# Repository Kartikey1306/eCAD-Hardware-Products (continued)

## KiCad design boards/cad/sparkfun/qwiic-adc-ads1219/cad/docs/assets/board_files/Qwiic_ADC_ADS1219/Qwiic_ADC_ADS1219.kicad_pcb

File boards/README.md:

# Boards Catalog

Development boards and kits relevant to the EmbeddedOS (EoS) ecosystem:
what the OS supports today, and where hardware/CAD work is heading.

Tracked by [#28](https://github.com/embeddedos-org/eCAD-Hardware-Products/issues/28)
("Development boards, kits, and CAD design-file reference"), which scopes the
full catalog across Arduino/AVR, Raspberry Pi, ESP32/ESP8266, STM32, Nordic,
FPGA, robotics, and AI-accelerator families.

## Boards with EoS descriptors today

These boards have first-class descriptors in
[`eos/boards/`](https://github.com/embeddedos-org/eos/tree/master/boards)
(`boards/*.yaml`: MCU, memory map, peripherals, linker script). The table
below is generated from those descriptors — the single source of truth.

| Board (descriptor) | MCU | Family | Vendor | Core |
|---|---|---|---|---|
| `am64x` | AM6442 | Sitara | Texas Instruments | cortex-a53 |
| `esp32` | ESP32-D0WDQ6 | ESP32 | Espressif | lx6 |
| `hiletgo-esp-wroom-32` | ESP32-D0WDQ6 | ESP32 | Espressif | lx6 |
| `imx8m` | MIMX8MM6 | i.MX8M | NXP | cortex-a53 |
| `nrf52840` | NRF52840 | nRF52 | Nordic Semiconductor | cortex-m4f |
| `qemu-arm64` | — | — | — | — |
| `raspberrypi4` | — | — | — | — |
| `samd51` | ATSAMD51J20A | SAMD51 | Microchip | cortex-m4f |
| `sifive_u` | FU740-C000 | HiFive | SiFive | u74 |
| `stm32f4` | STM32F407VG | STM32F4 | ST Microelectronics | cortex-m4 |
| `stm32h743` | — | — | ST Microelectronics | — |
| `stm32mp1` | — | — | ST Microelectronics | — |
| `tms570` | TMS570LC4357 | TMS570 | Texas Instruments | cortex-r5f |

("—" = not specified in the descriptor; contributions welcome.)

## Generic targets

Beyond the named boards, `eos/boards/` ships 71 `generic-*` descriptors
covering CPU families without a specific board attached (e.g.
`generic-cortex-m4`, `generic-esp32s3`, `generic-riscv*`, `generic-avr`,
`generic-8051`). These are the bring-up starting point for a new board in
the same family: copy the closest generic descriptor, fill in the concrete
MCU, memory map, and peripherals, and submit it against `eos`.

## Adding a board

1. Add `boards/<name>.yaml` in `eos` following the existing schema
   (`board.name/mcu/family/arch/core/vendor/clock_hz/memory/peripherals`).
2. If this repo should carry the CAD side (schematic, PCB, 3D model),
   open an issue here referencing the `eos` descriptor and attach the
   design files under the matching `*_CAD_Design/` domain directory.

## Incoming (no EoS descriptor yet) — October 2026

Boards on the #28 watchlist with no `eos/boards/` descriptor yet. Entries
stay here (not in the table above) until a descriptor lands; specs are
minimal until datasheet review.

| Board | Vendor | Family | Notes |
|---|---|---|---|
| FRDM-IMXRT1186 | NXP | i.MX RT1186 | FRDM dev board: M7 @ 800MHz + M33 @ 300MHz, dual GbE TSN + 2× Fast Eth (EtherCAT/TSN), motor-control headers — the eNet deterministic-comms reference target |
| ESP32-C5 Pico | Espressif | ESP32-C5 | RISC-V + 802.15.4/Wi-Fi 6; Thread/Matter candidate |
| ESP-Mosaico (S31) | — | — | Specs pending datasheet review |
| Arduino VENTUNO Q | Arduino | Dragonwing IQ-8275 + STM32H5F5 | Dual-brain: Qualcomm Dragonwing IQ-8275 + STM32H5F5, 16GB RAM, 3× MIPI-CSI, CAN FD, ROS 2 — the dual-brain pattern in hardware |
| DEBIX M8391-01 | DEBIX | MediaTek Genio 720 | Octa-core A78/A55, 9-TOPS NPU850, industrial -40..85°C, Pi-sized — mid-tier NPU vision/robotics target |
| Bluemag Pi | Upbeat | SiFive E3 + E2 | RISC-V flight controller (E3 flight-critical + E2 AI/system), onboard AI; CEATEC Oct 13–16 demo — aero dual-brain COTS reference |
| Alif StartKit SK-E1C | Alif | Ensemble E1C | Cortex-M55 + Ethos-U55, 2MB SRAM, Arducam header, dual PDM mics, onboard J-Link — tinyML reference target |
| Alif StartKit SK-B1 | Alif | Ensemble E1 | As E1C + BLE 5.3 + 802.15.4 |
| NuMaker-IoT-MA35D0-A2 "Chili Pro" | Nuvoton | MA35D0 | Dual Cortex-A35 650MHz + Cortex-M4 180MHz; 45×45mm heterogeneous Linux+MCU eval board |
| M5Stack Stamp LoRa-1262 / Module13.2 | M5Stack | ESP32-S3 | SX1262, 868–923MHz LoRa; pairs with the eNet LoRaWAN study |
| 8devices 8Sight T100 | 8devices | STM32N657 | Cortex-M55 800MHz + 600-GOPS Neural-ART NPU + HW ISP; Lynred LWIR, 320×240@60fps fully offline — NPU-vision reference design |
| AIM-M-H10 | Geniatech | Hailo-10 | M.2 2280 M-Key AI accelerator card: Hailo-10 at up to 40 TOPS, up to 16GB on-module LPDDR4/4X, PCIe host link, ~12W — the M.2-keyed accelerator pattern for M.2-bearing watchlist hosts; vendor figures per the Geniatech product page, pending datasheet review |
| AIM-M-R28 | Geniatech | Rockchip RK1828 | M.2 2280 M-Key AI accelerator card: RK1828 coprocessor at 20 TOPS INT8 with 5GB in-package DRAM, PCIe 2.1 x1, 20W TDP, -25..85°C — local LLM/VLM inference aimed at Rockchip hosts (RK3568/3576/3588); vendor figures per the Geniatech product page, pending datasheet review |
| Raspberry Pi Smart Display Module | Raspberry Pi | Compute Module 5 carrier (Intel SDM-L) | $30 CM5 carrier in the Intel SDM-L form factor, built for digital signage and kiosks: HDMI 2.0 out, GbE, M.2 M-key (NVMe or an AI accelerator), MIPI DSI/CSI-2; vendor lifecycle "available until at least January 2036". The commercial CM5-carrier counterpart to the org's original [eos-cm5-base](eos/eos-cm5-base/README.md) — not a mirror candidate (no redistributable CAD published), recorded here as the signage/kiosk reference |
| Orange Pi O1 | Orange Pi | SOPHGO BM1688 | AI-vision SBC: octa-core Cortex-A53 @ 1.65GHz + RISC-V C906 co-processor, 16 TOPS INT8 TPU, up to 16x 1080p30 decode, 8/16GB LPDDR4/X, dual GbE, Wi-Fi 6E, M.2 M-key NVMe + M.2 B-key (4G/5G) — watchlist entry, specs per CNX Software's 2026-10-15 report, pending datasheet review; the same BM1688 SoC is an eAI silicon-roster candidate |
| HPMicro HPM5151 (MCU family — no board yet) | HPMicro | HPM5100 series | Silicon-family watchlist entry, not a board record: 400 MHz RISC-V (up to 480 MHz), 416 KB SRAM, 1 MB flash, 4× 16-bit ADCs, 4× op-amps, 4× comparators, USB 2.0 OTG + PHY, CAN FD, 32 PWM channels, HW FPU/SIMD/DSP, 3.57 CoreMark/MHz — motor-control / mixed-signal analog niche; specs per CNX Software's report, pending datasheet review |

## Design files

[`cad/`](cad/) holds the published CAD design of every catalogued board whose licence
allows redistribution: every CAD file in the manufacturer's repository at the commit its
record pins, in the manufacturer's folder layout. That means Eagle, KiCad, Altium, OrCAD
and Allegro sources, projects and libraries, Gerber and drill files, and STEP, IGES, STL,
VRML and DXF models; archives are unpacked to their CAD members. Each file is
byte-identical to its recorded digest or to its git blob at that commit, and each board's
`ATTRIBUTION.md` credits the manufacturer, names the licence and lists what was left out.
Documents (PDFs, BOMs, readmes) are never copied. How it is built and checked:
[docs/devboard-cad-database.md](../docs/devboard-cad-database.md#mirror).

## Roadmap (from #28)

- Per-family pages (Arduino, Pi, ESP32, STM32, nRF, FPGA, robotics kits)
  with CAD design-file references.
- Mapping each catalog entry to its EoS support tier (descriptor,
  BSP, EoSim model).
- Kit/cookbook entries: "what to buy to run EoS on <board>".

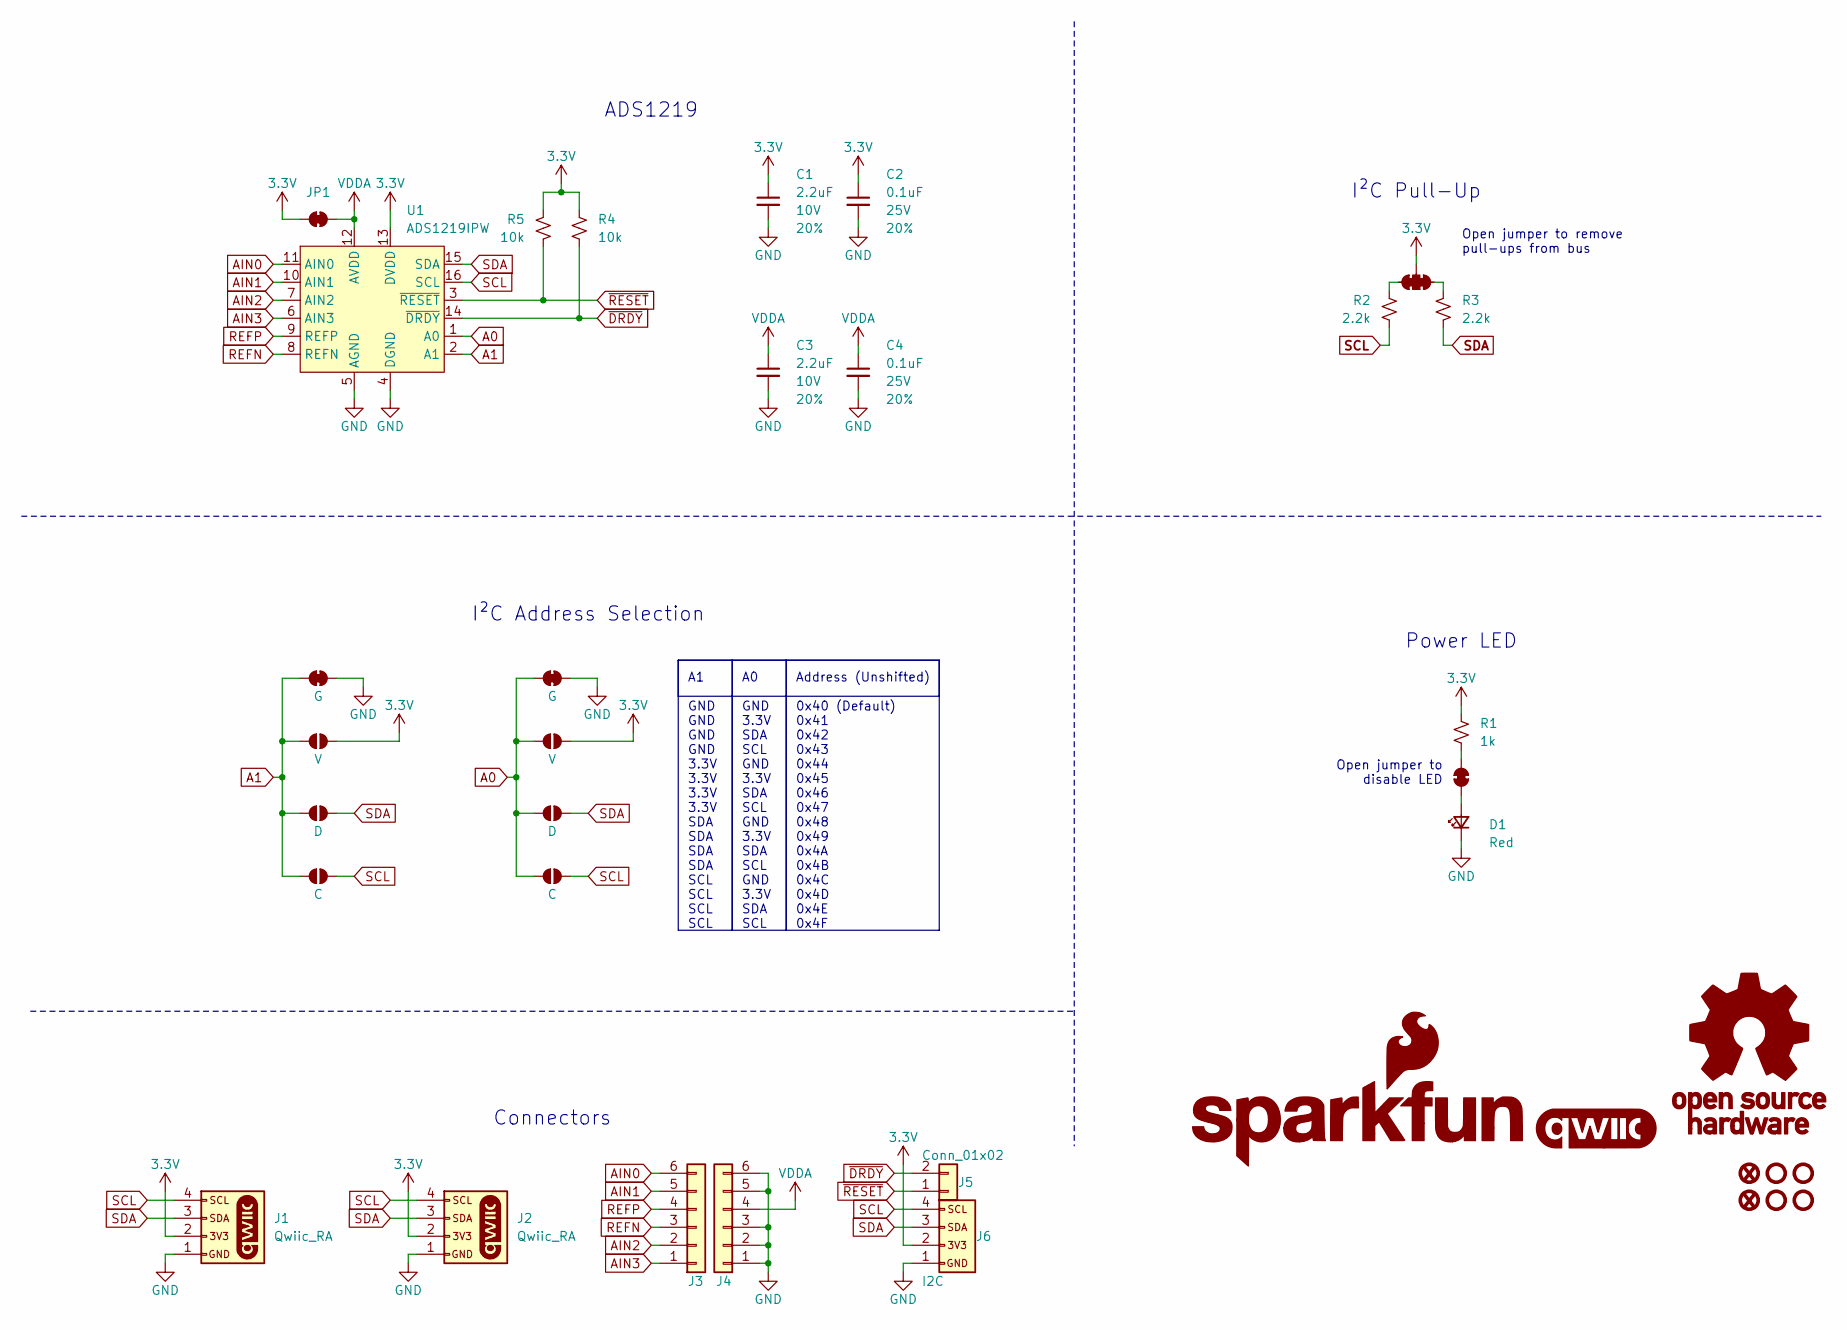
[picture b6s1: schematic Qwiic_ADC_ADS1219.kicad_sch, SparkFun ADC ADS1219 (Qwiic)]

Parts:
C1, C3: 2.2uF; C_0603_1608Metric; Voltage 10V; Tolerance 20%
C2, C4: 0.1uF; C_0603_1608Metric; Voltage 25V; Tolerance 20%
D1: Red; LED_0603_1608Metric_Red
FID1, FID3: Fiducial_0.5mm; Fiducial_0.5mm_Mask1mm
G1: SparkFun_Logo
J1, J2: Qwiic_RA; JST_SMD_1.0mm-4_Black
J3, J4: Conn_01x06; 1x06
J5: Conn_01x02; 1x02
J6: I2C; 1x04
JP1, JP2: Jumper_2_NC_Trace
JP3: Jumper_3_NC-2_Trace
JP4, JP8: G; Jumper_2_NC_Trace
JP5, JP9: V; Jumper_2_NO
JP6, JP10: D; Jumper_2_NO
JP7, JP11: C; Jumper_2_NO
R1: 1k; R_0603_1608Metric
R2, R3: 2.2k; R_0603_1608Metric
R4, R5: 10k; R_0603_1608Metric
ST1, ST2, ST3, ST4: Standoff
U1: ADS1219IPW; TSSOP-16

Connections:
3.3V: C1.1, C2.1, J1.2, J2.2, J6.2, JP1.1 (A), JP3.2 (B), JP5.2 (B), JP9.2 (B), R1.2, R4.2, R5.1, U1.13 (DVDD)
A0: JP4.1 (A), JP5.1 (A), JP6.1 (A), JP7.1 (A), U1.1 (A0)
A1: JP8.1 (A), JP9.1 (A), JP10.1 (A), JP11.1 (A), U1.2 (A1)
AIN0: J3.6, U1.11 (AIN0)
AIN1: J3.5, U1.10 (AIN1)
AIN2: J3.2, U1.7 (AIN2)
AIN3: J3.1, U1.6 (AIN3)
GND: C1.2, C2.2, C3.2, C4.2, D1.1 (K), J1.1, J2.1, J4.1, J4.2, J4.3, J4.5, J4.6, J6.1, JP4.2 (B), JP8.2 (B), U1.4 (DGND), U1.5 (AGND)
unnamed: D1.2 (A), JP2.1 (A)
unnamed: JP2.2 (B), R1.1
unnamed: JP3.1 (A), R3.1
unnamed: JP3.3 (C), R2.2
REFN: J3.3, U1.8 (REFN)
REFP: J3.4, U1.9 (REFP)
SCL: J1.4, J2.4, J6.4, JP7.2 (B), JP11.2 (B), R2.1, U1.16 (SCL)
SDA: J1.3, J2.3, J6.3, JP6.2 (B), JP10.2 (B), R3.2, U1.15 (SDA)
VDDA: C3.1, C4.1, J4.4, JP1.2 (B), U1.12 (AVDD)
~DRDY: J5.2, R4.1, U1.14 (~DRDY)
~RESET: J5.1, R5.2, U1.3 (~RESET)

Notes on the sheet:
Open jumper to remove pull-ups from bus
Connectors
Power LED
I²C Address Selection
Open jumper to disable LED
A1 GND GND GND GND 3.3V 3.3V 3.3V 3.3V SDA SDA SDA SDA SCL SCL SCL SCL
Address (Unshifted) 0x40 (Default) 0x41 0x42 0x43 0x44 0x45 0x46 0x47 0x48 0x49 0x4A 0x4B 0x4C 0x4D 0x4E 0x4F
ADS1219
I²C Pull-Up
A0 GND 3.3V SDA SCL GND 3.3V SDA SCL GND 3.3V SDA SCL GND 3.3V SDA SCL

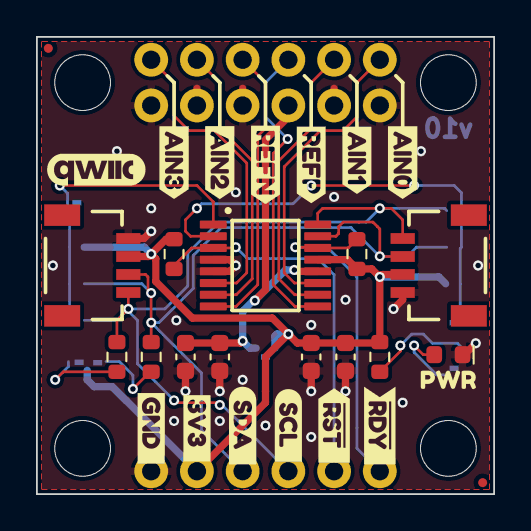
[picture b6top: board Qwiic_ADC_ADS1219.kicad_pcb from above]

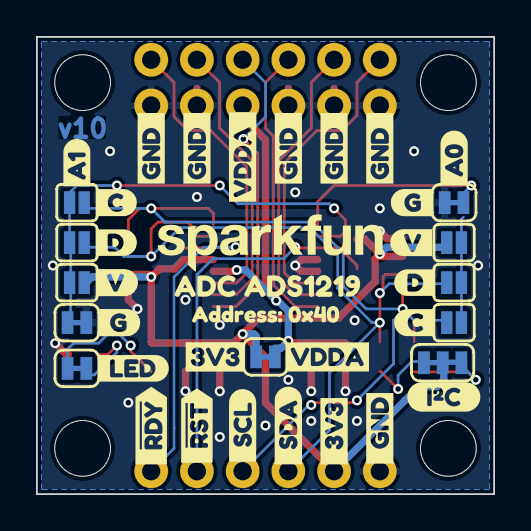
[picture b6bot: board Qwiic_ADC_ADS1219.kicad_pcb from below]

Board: 2 copper layers, 25.4 x 25.4 mm, 75 parts (39 on the bottom side), 19 nets.

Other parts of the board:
kibuzzard-64C3B30F: G***; kibuzzard-64C3B30F
kibuzzard-64C3BD7A: G***; kibuzzard-64C3BD7A
kibuzzard-64C36D1A: G***; kibuzzard-64C36D1A
kibuzzard-64C36D2D: G***; kibuzzard-64C36D2D
kibuzzard-64C36D5B: G***; kibuzzard-64C36D5B
kibuzzard-64C36D6C: G***; kibuzzard-64C36D6C
kibuzzard-64C36D47: G***; kibuzzard-64C36D47
kibuzzard-64C36D91: G***; kibuzzard-64C36D91
kibuzzard-64C37A88: G***; kibuzzard-64C37A88
kibuzzard-64C37CC9: G***; kibuzzard-64C37CC9
kibuzzard-64C38090: G***; kibuzzard-64C38090
kibuzzard-67BCC03F: G***; kibuzzard-67BCC03F
kibuzzard-67BCE7E0: G***; kibuzzard-67BCE7E0
kibuzzard-67BCE9A5: G***; kibuzzard-67BCE9A5
kibuzzard-67BCE9C9: G***; kibuzzard-67BCE9C9
kibuzzard-67BCE9CD: G***; kibuzzard-67BCE9CD
kibuzzard-67BCE9E1: G***; kibuzzard-67BCE9E1
kibuzzard-67BCE80E: G***; kibuzzard-67BCE80E
kibuzzard-67BCE89D: G***; kibuzzard-67BCE89D
kibuzzard-67BCE805: G***; kibuzzard-67BCE805
kibuzzard-67BCE809: G***; kibuzzard-67BCE809
kibuzzard-67BCE889: G***; kibuzzard-67BCE889
kibuzzard-67BCE896: G***; kibuzzard-67BCE896
kibuzzard-67BCE899: G***; kibuzzard-67BCE899
kibuzzard-67BCEA1E: G***; kibuzzard-67BCEA1E
kibuzzard-67BCEA3A: G***; kibuzzard-67BCEA3A
kibuzzard-67BCEA31: G***; kibuzzard-67BCEA31
kibuzzard-67BCEA48: G***; kibuzzard-67BCEA48
kibuzzard-67BCEA55: G***; kibuzzard-67BCEA55
kibuzzard-67BCEA65: G***; kibuzzard-67BCEA65
kibuzzard-67BCEA70: G***; kibuzzard-67BCEA70
kibuzzard-67BCEAAB: G***; kibuzzard-67BCEAAB
kibuzzard-67BCEAC6, kibuzzard-67BCEAC6#2, kibuzzard-67BCEAC6#3, kibuzzard-67BCEAC6#4, kibuzzard-67BCEAC6#5: G***; kibuzzard-67BCEAC6
kibuzzard-67BCEAE1: G***; kibuzzard-67BCEAE1
kibuzzard-67BCEB1D: G***; kibuzzard-67BCEB1D
kibuzzard-67BCEB15: G***; kibuzzard-67BCEB15
kibuzzard-67BCEB32: G***; kibuzzard-67BCEB32

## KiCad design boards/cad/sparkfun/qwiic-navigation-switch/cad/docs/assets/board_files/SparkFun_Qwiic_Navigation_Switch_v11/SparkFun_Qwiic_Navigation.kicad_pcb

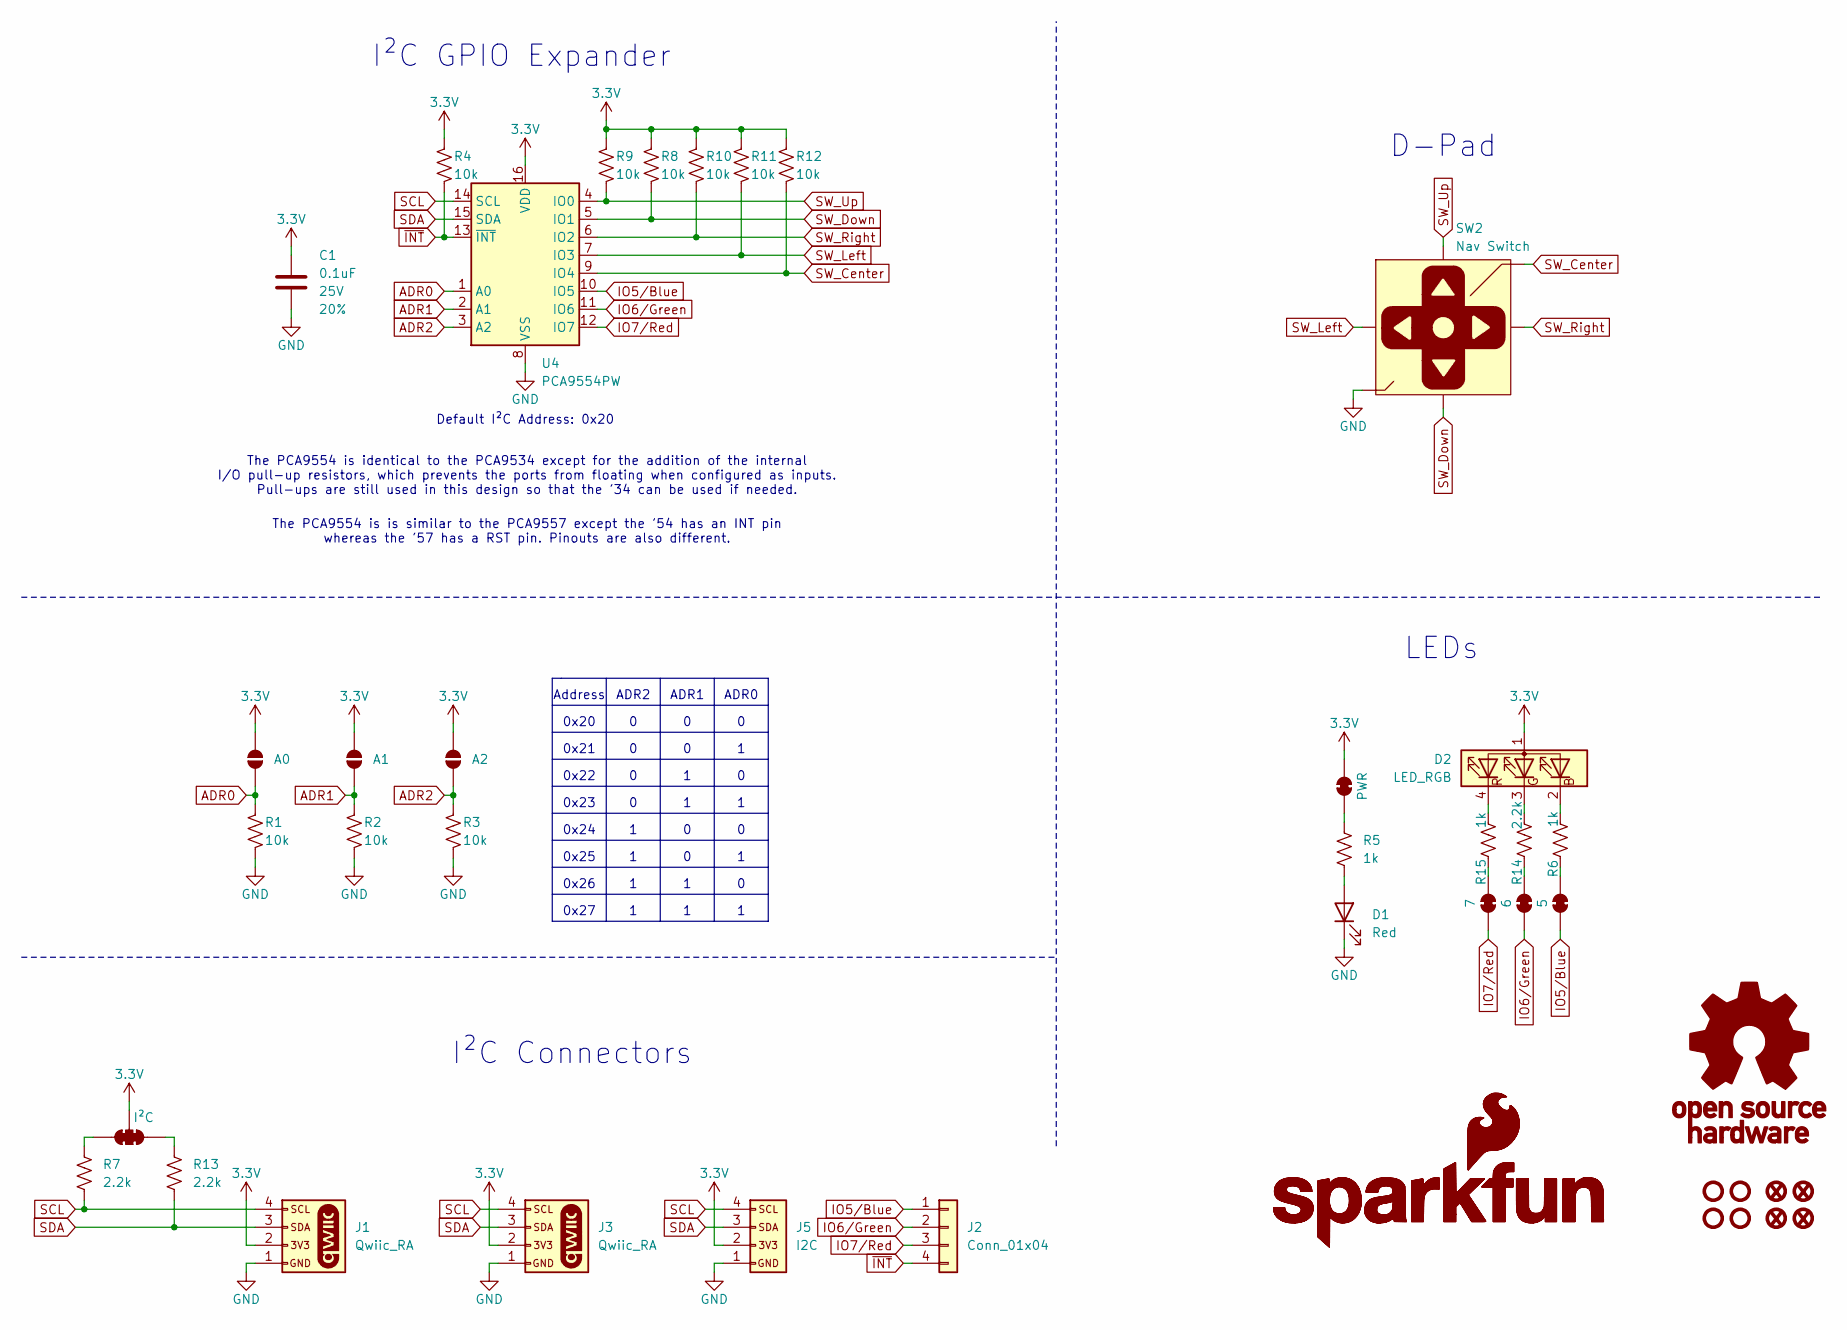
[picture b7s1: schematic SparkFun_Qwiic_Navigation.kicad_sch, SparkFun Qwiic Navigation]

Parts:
C1: 0.1uF; C_0603_1608Metric; Voltage 25V; Tolerance 20%
D1: Red; LED_0603_1608Metric_Red
D2: LED_RGB; LED_1205_RGB_Bottom
FID1, FID2, FID3, FID4: Fiducial_0.5mm; Fiducial_0.5mm_Mask1mm
G1: OSHW_Logo; Creative_Commons_License
G3: SparkFun_Logo
G5: SparkFun_Logo; SparkFun_Logo_8mm
J1, J3: Qwiic_RA; JST_SMD_1.0mm-4_RA
J2: Conn_01x04; 1x04
J5: I2C; 1x04
JP1: A0; Jumper_2_NO
JP2: A1; Jumper_2_NO
JP3: A2; Jumper_2_NO
JP4: PWR; Jumper_2_NC_Trace
JP5: 5; Jumper_2_NC_Trace
JP6: I²C; Jumper_3_NC-2_Trace
JP7: 6; Jumper_2_NC_Trace
JP8: 7; Jumper_2_NC_Trace
R1, R2, R3, R4, R8, R9, R10, R11, R12: 10k; R_0603_1608Metric
R5, R6, R15: 1k; R_0603_1608Metric
R7, R13, R14: 2.2k; R_0603_1608Metric
ST1, ST2, ST3, ST4: Standoff
SW2: Nav Switch; Navigation_SMD_7.5x7.5mm
U4: PCA9554PW; TSSOP-16_4.4x5mm_P0.65mm

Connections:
3.3V: C1.1, D2.1 (A), J1.2, J3.2, J5.2, JP1.2 (B), JP2.2 (B), JP3.2 (B), JP4.2 (B), JP6.2 (C), R4.2, R8.2, R9.2, R10.2, R11.2, R12.2, U4.16 (VDD)
ADR0: JP1.1 (A), R1.2, U4.1 (A0)
ADR1: JP2.1 (A), R2.2, U4.2 (A1)
ADR2: JP3.1 (A), R3.2, U4.3 (A2)
GND: C1.2, D1.1 (K), J1.1, J3.1, J5.1, R1.1, R2.1, R3.1, SW2.2 (GND), U4.8 (VSS)
IO5/Blue: J2.1, JP5.2 (B), U4.10 (IO5)
IO6/Green: J2.2, JP7.2 (B), U4.11 (IO6)
IO7/Red: J2.3, JP8.2 (B), U4.12 (IO7)
unnamed: D1.2 (A), R5.2
unnamed: D2.2 (BK), R6.2
unnamed: D2.3 (GK), R14.2
unnamed: D2.4 (RK), R15.2
unnamed: JP4.1 (A), R5.1
unnamed: JP5.1 (A), R6.1
unnamed: JP6.1 (A), R13.1
unnamed: JP6.3 (B), R7.1
unnamed: JP7.1 (A), R14.1
unnamed: JP8.1 (A), R15.1
SCL: J1.4, J3.4, J5.4, R7.2, U4.14 (SCL)
SDA: J1.3, J3.3, J5.3, R13.2, U4.15 (SDA)
SW_Center: R12.1, SW2.5 (Center), U4.9 (IO4)
SW_Down: R8.1, SW2.3 (Down), U4.5 (IO1)
SW_Left: R11.1, SW2.1 (Left), U4.7 (IO3)
SW_Right: R10.1, SW2.4 (Right), U4.6 (IO2)
SW_Up: R9.1, SW2.6 (Up), U4.4 (IO0)
~INT: J2.4, R4.1, U4.13 (~INT)

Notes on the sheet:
The PCA9554 is is similar to the PCA9557 except the '54 has an INT pin whereas the '57 has a RST pin. Pinouts are also different.
Default I²C Address: 0x20
I²C GPIO Expander
0x20
I²C Connectors
ADR2
ADR0
0x23
The PCA9554 is identical to the PCA9534 except for the addition of the internal I/O pull-up resistors, which prevents the ports from floating when configured as inputs. Pull-ups are still used in this design so that the '34 can be used if needed.
0x22
LEDs
0x25
0x26
0x24
D-Pad
0x27
ADR1
0x21
Address

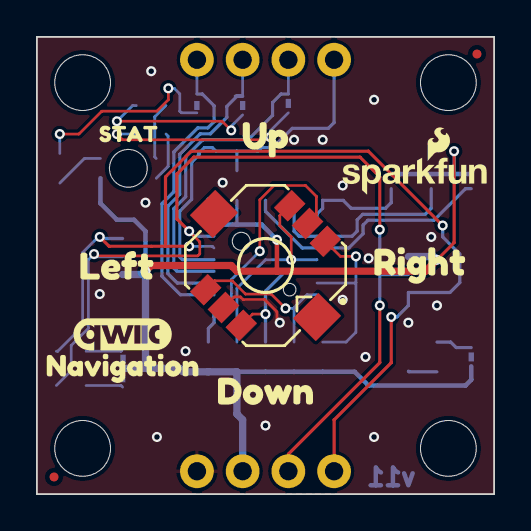
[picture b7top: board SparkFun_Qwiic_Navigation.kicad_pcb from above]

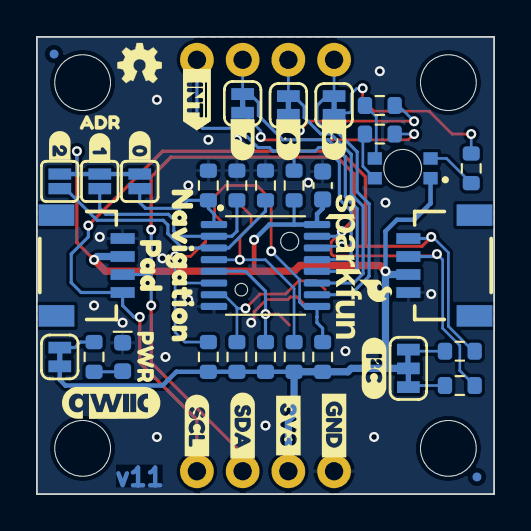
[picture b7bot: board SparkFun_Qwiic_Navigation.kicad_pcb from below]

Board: 2 copper layers, 25.4 x 25.4 mm, 64 parts (48 on the bottom side), 26 nets.

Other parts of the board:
Ref**: Val**; OSHW_Logo_2.5mm
kibuzzard-64C2E6A3: G***; kibuzzard-64C2E6A3
kibuzzard-66EED5D2: G***; kibuzzard-66EED5D2
kibuzzard-66EF6B89: G***; kibuzzard-66EF6B89
kibuzzard-66EF7A0B: G***; kibuzzard-66EF7A0B
kibuzzard-66EF7A03: G***; kibuzzard-66EF7A03
kibuzzard-66EF7A24: G***; kibuzzard-66EF7A24
kibuzzard-66EF7AE6: G***; kibuzzard-66EF7AE6
kibuzzard-66EF7AEF: G***; kibuzzard-66EF7AEF
kibuzzard-66EF7B1E: G***; kibuzzard-66EF7B1E
kibuzzard-66EF7B7C: G***; kibuzzard-66EF7B7C
kibuzzard-66EF7B15: G***; kibuzzard-66EF7B15
kibuzzard-66EF55AC: G***; kibuzzard-66EF55AC
kibuzzard-66EF79E9: G***; kibuzzard-66EF79E9
kibuzzard-66EF559E: G***; kibuzzard-66EF559E
kibuzzard-66EF5597: G***; kibuzzard-66EF5597
kibuzzard-66F18F5E: G***; kibuzzard-66F18F5E
kibuzzard-66F18F8F: G***; kibuzzard-66F18F8F
kibuzzard-66F18F9B: G***; kibuzzard-66F18F9B
kibuzzard-66F182A6: G***; kibuzzard-66F182A6
kibuzzard-675B45F7: G***; kibuzzard-675B45F7
kibuzzard-67117BDD: G***; kibuzzard-67117BDD
kibuzzard-6730262A: G***; kibuzzard-6730262A

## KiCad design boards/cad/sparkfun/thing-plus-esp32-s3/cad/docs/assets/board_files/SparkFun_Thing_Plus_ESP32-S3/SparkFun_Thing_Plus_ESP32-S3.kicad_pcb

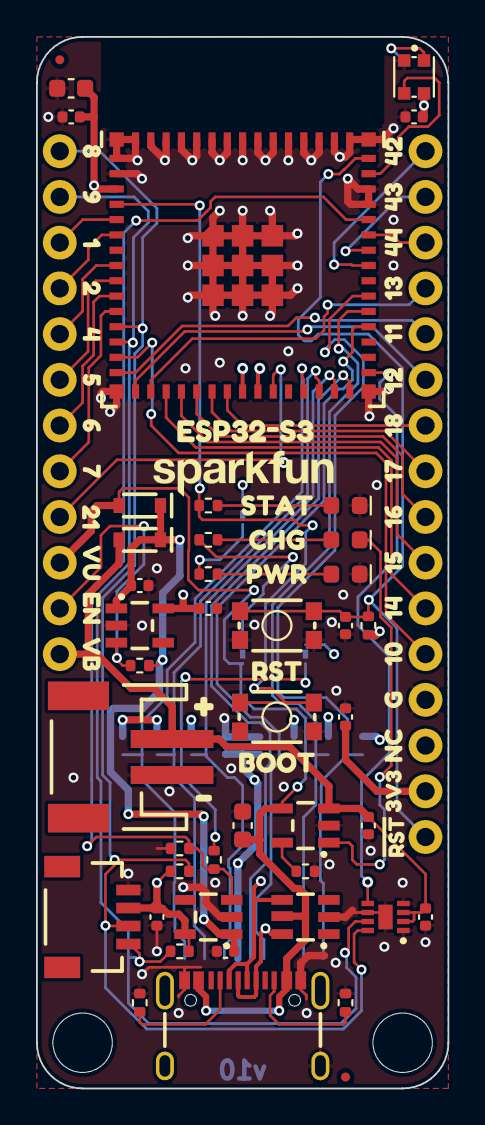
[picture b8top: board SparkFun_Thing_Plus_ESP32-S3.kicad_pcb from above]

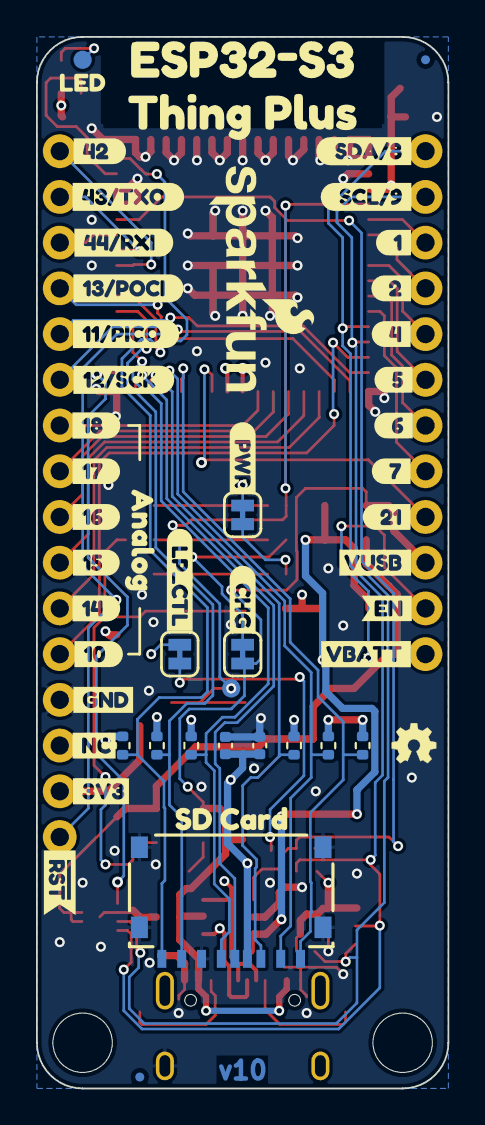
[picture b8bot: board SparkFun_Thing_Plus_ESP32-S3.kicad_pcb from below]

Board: 4 copper layers, 22.9 x 58.4 mm, 137 parts (53 on the bottom side), 53 nets.

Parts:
C1: 22uF; C_0603_1608Metric
C2, C5, C8, C11: 0.1uF; C_0402_1005Metric
C3, C4: 10uF; C_0402_1005Metric
C6, C13: 1.0uF; C_0402_1005Metric
C7, C12: 4.7uF; C_0402_1005Metric
C9: 4.7uF; C_0603_1608Metric
C10, C14: 2.2uF; C_0402_1005Metric
D1: Green; LED_0603_1608Metric
D2, D3: BAT60A; SOD-323
D4: Yellow; LED_0603_1608Metric
D5: Red; LED_0603_1608Metric
D6: WS2812B; WS2812-2020
FID1, FID2, FID3, FID4: Fiducial_0.5mm; Fiducial_0.5mm_Mask1mm
G3: OSHW_Logo; Creative_Commons_License
J1: USB_C_Receptacle; USB-C_16
J2: microSD_Friction; microSD_Friction_Fit_Atom
J3: JST_2mm_LiPo; JST_SMD_2.0mm-2
J4: Qwiic_RA; JST_SMD_1.0mm-4_RA
JP1, JP2, JP3: Jumper_2_NC_Trace
R1, R2, R3, R4, R5, R6, R8, R17: 10k; R_0402_1005Metric
R7: 330; R_0402_1005Metric
R9: 4.7k; R_0402_1005Metric
R10, R11: 5.1k; R_0402_1005Metric
R12, R15: 2.2k; R_0402_1005Metric
R13, R19: 100k; R_0402_1005Metric
R14: 1k; R_0402_1005Metric
R16: 2.0k; R_0402_1005Metric
Ref**: Val**; OSHW_Logo_2.5mm
ST1, ST3: Standoff
SW1, SW2: SMD_4.6x2.8mm_h2.5mm; Momentary_SMD_4.6x2.8mm_h2.5mm
TP1, TP2: 1.0mm; TestPoint-1.0mm
U1, U6: RT9080-3.3; SOT23-5
U2: DT1042-04SO; SOT23-6
U3: ESP32-S3-MINI; ESP32-MINI
U4: MAX17048; DFN-8
U5: MCP73831; SOT23-5
U9: Ordering_Instructions
U10: ThingPlus
kibuzzard-65A99A9C: G***; kibuzzard-65A99A9C
kibuzzard-65A99AA3: G***; kibuzzard-65A99AA3
kibuzzard-65A99E72: G***; kibuzzard-65A99E72
kibuzzard-65A403E0: G***; kibuzzard-65A403E0
kibuzzard-65A992E3: G***; kibuzzard-65A992E3
kibuzzard-65A9923A: G***; kibuzzard-65A9923A
kibuzzard-65A9926C: G***; kibuzzard-65A9926C
kibuzzard-65A9926F: G***; kibuzzard-65A9926F
kibuzzard-65A9927C: G***; kibuzzard-65A9927C
kibuzzard-65A9927F: G***; kibuzzard-65A9927F
kibuzzard-65A9928A: G***; kibuzzard-65A9928A
kibuzzard-65A9928E: G***; kibuzzard-65A9928E
kibuzzard-65A9933C: G***; kibuzzard-65A9933C
kibuzzard-65A9934B: G***; kibuzzard-65A9934B
kibuzzard-65A9935C: G***; kibuzzard-65A9935C
kibuzzard-65A9936B: G***; kibuzzard-65A9936B
kibuzzard-65A9990D: G***; kibuzzard-65A9990D
kibuzzard-65A99252: G***; kibuzzard-65A99252
kibuzzard-65A99268: G***; kibuzzard-65A99268
kibuzzard-65A99274: G***; kibuzzard-65A99274
kibuzzard-65A99278: G***; kibuzzard-65A99278
kibuzzard-65A99283: G***; kibuzzard-65A99283
kibuzzard-65A99287: G***; kibuzzard-65A99287
kibuzzard-65A99292: G***; kibuzzard-65A99292
kibuzzard-65A99297: G***; kibuzzard-65A99297
kibuzzard-65A99335: G***; kibuzzard-65A99335
kibuzzard-65A99346: G***; kibuzzard-65A99346
kibuzzard-65A99350: G***; kibuzzard-65A99350
kibuzzard-65A99354: G***; kibuzzard-65A99354
kibuzzard-65A99359: G***; kibuzzard-65A99359
kibuzzard-65A99360: G***; kibuzzard-65A99360
kibuzzard-65A99364: G***; kibuzzard-65A99364
kibuzzard-65A99367: G***; kibuzzard-65A99367
kibuzzard-65A99912: G***; kibuzzard-65A99912
kibuzzard-65A99933: G***; kibuzzard-65A99933
kibuzzard-65AA9C9F: G***; kibuzzard-65AA9C9F
kibuzzard-656A3D93: G***; kibuzzard-656A3D93
kibuzzard-656A31AF: G***; kibuzzard-656A31AF
kibuzzard-656A32A0: G***; kibuzzard-656A32A0
kibuzzard-656A32FE: G***; kibuzzard-656A32FE
kibuzzard-656A35A5: G***; kibuzzard-656A35A5
kibuzzard-656A35AD: G***; kibuzzard-656A35AD
kibuzzard-656A35B5: G***; kibuzzard-656A35B5
kibuzzard-656A35BC: G***; kibuzzard-656A35BC
kibuzzard-656A35C4: G***; kibuzzard-656A35C4
kibuzzard-656A36A2: G***; kibuzzard-656A36A2
kibuzzard-656A36A7: G***; kibuzzard-656A36A7
kibuzzard-656A36C2: G***; kibuzzard-656A36C2
kibuzzard-656A47C5: G***; kibuzzard-656A47C5
kibuzzard-656A359E: G***; kibuzzard-656A359E
kibuzzard-656A361F: G***; kibuzzard-656A361F
kibuzzard-656A367B: G***; kibuzzard-656A367B
kibuzzard-656A368C: G***; kibuzzard-656A368C
kibuzzard-656A482A: G***; kibuzzard-656A482A
kibuzzard-656A3526: G***; kibuzzard-656A3526
kibuzzard-656A3552: G***; kibuzzard-656A3552
kibuzzard-656A3559: G***; kibuzzard-656A3559
kibuzzard-656A3560: G***; kibuzzard-656A3560
kibuzzard-656A3567: G***; kibuzzard-656A3567
kibuzzard-656A3591: G***; kibuzzard-656A3591
kibuzzard-656A3598: G***; kibuzzard-656A3598
kibuzzard-656A3668: G***; kibuzzard-656A3668
kibuzzard-656A3687: G***; kibuzzard-656A3687
kibuzzard-656A3691: G***; kibuzzard-656A3691
kibuzzard-656A3878: G***; kibuzzard-656A3878
kibuzzard-656A4896: G***; kibuzzard-656A4896
kibuzzard-6569BE4A: G***; kibuzzard-6569BE4A
kibuzzard-6569BE28: G***; kibuzzard-6569BE28
kibuzzard-6569BE57: G***; kibuzzard-6569BE57
kibuzzard-6569BF02: G***; kibuzzard-6569BF02
kibuzzard-6569F7FC: G***; kibuzzard-6569F7FC
kibuzzard-6569F8A4: G***; kibuzzard-6569F8A4

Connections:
3.3V: C1.2, C7.1, C11.1, C13.1, JP1.2 (B), JP2.2 (B), R8.1, U3.3 (3V3), U6.5 (VOUT), U10.27 (3.3V)
3.3V_P: C3.1, C4.1, C5.1, C8.1, D6.4 (VDD), J2.4 (VDD), J4.2, R1.1, R2.1, R3.1, R4.1, R5.1, R6.1, R12.1, R15.1, U1.5 (VOUT)
EN: R13.2, U6.3 (EN), U10.11 (EN)
ESP0/STAT: R7.1, SW1.1 (A), TP2.1, U3.4 (IO0)
ESP1: U3.5 (IOA1), U10.3 (GPIO6)
ESP2: U3.6 (IOA2), U10.4 (GPIO5)
ESP4: U3.8 (IOA4), U10.5 (GPIO4)
ESP5: U3.9 (IOA5), U10.6 (GPIO3)
ESP6: U3.10 (IOA6), U10.7 (GPIO2)
ESP7: U3.11 (IOA7), U10.8 (GPIO1)
ESP8/SDA: J4.3, R15.2, U3.12 (IOA8), U4.8 (SDA), U10.1 (SDA)
ESP9/SCL: J4.4, R12.2, U3.13 (IOA9), U4.7 (SCL), U10.2 (SCL)
ESP10/A0: U3.14 (IOA10), U10.24 (A0)
ESP11/PICO: U3.15 (IOA11), U10.17 (PICO)
ESP12/SCK: U3.16 (IOA12), U10.18 (SCK)
ESP13/POCI: U3.17 (IOA13), U10.16 (POCI)
ESP14/A1: U3.18 (IOA14), U10.23 (A1)
ESP15/A2: U3.19 (IOA15), U10.22 (A2)
ESP16/A3: U3.20 (IOA16), U10.21 (A3)
ESP17/A4: U3.21 (IOA17), U10.20 (A4)
ESP18/A5: U3.22 (IOA18), U10.19 (A5)
ESP19/D-: J1.A7 (D-), J1.B7 (D-), U2.4 (I/O3), U3.23 (IOA19)
ESP20/D+: J1.A6 (D+), J1.B6 (D+), U2.6 (I/O4), U3.24 (IOA20)
ESP21: U3.25 (IO21), U10.9 (GPIO0)
ESP33/SDIO3: J2.2 (DAT3/~CS), R6.2, U3.28 (IO33)
ESP34/SDIO_CMD: J2.3 (CMD/SDI), R1.2, U3.29 (IO34)
ESP35/~ALRT: U3.31 (IO35), U4.5 (~ALRT)
ESP38/SDIO_CLK: J2.5 (CLK/SCK), R2.2, U3.34 (IO38)
ESP39/SDIO0: J2.7 (DAT0/SDO), R3.2, U3.35 (IO39)
ESP40/SDIO1: J2.8 (DAT1), R4.2, U3.36 (IO40)
ESP42/FREE: U3.38 (IO42), U10.13 (FREEBIE)
ESP43/TXO: U3.39 (TXD0/IO43), U10.14 (TX)
ESP44/RXI: U3.40 (RXD0/IO44), U10.15 (RX)
ESP45/Q_EN: R17.2, R19.1, U1.3 (EN), U3.41 (IO45)
ESP46/LED: D6.3 (DIN), U3.44 (IO46)
ESP47/SDIO2: J2.1 (DAT2), R5.2, U3.27 (IO47)
ESP48/SDIO_~DET: J2.9 (DET), U3.30 (IO48)
ESP~RST: C6.1, R8.2, SW2.1 (A), U3.45 (EN), U10.28 (~RESET)
GND: C1.1, C2.2, C3.2, C4.2, C5.2, C6.2, C7.2, C8.2, C9.2, C10.2, C11.2, C12.2, C13.2, C14.2, D1.1 (K), D5.1 (K), D6.2 (VSS), J1.GND, J1.S (SHIELD), J2.6 (VSS), J2.10 (SHIELD), J3.1 (-), J4.1, R10.1, R11.2, R16.2, R19.2, SW1.2 (B), SW2.2 (B), U1.2 (GND), U2.2 (GND), U3.1 (GND), U3.2 (GND), U3.42 (GND), U3.43 (GND), U3.46 (GND), U3.47 (GND), U3.48 (GND), U3.49 (GND), U3.50 (GND), U3.51 (GND), U3.52 (GND), U3.53 (GND), U3.54 (GND), U3.55 (GND), U3.56 (GND), U3.57 (GND), U3.58 (GND), U3.59 (GND), U3.60 (GND), U3.61 (GND), U3.62 (GND), U3.63 (GND), U3.64 (GND), U3.65 (GND), U4.1 (CTG), U4.4 (GND), U4.6 (QSTRT), U4.9 (GND), U5.2 (GND), U6.2 (GND), U10.25 (GND)
unnamed: D1.2 (A), R7.2
unnamed: D4.2 (A), R14.1
unnamed: D4.1 (K), U5.1 (STAT)
unnamed: D5.2 (A), R9.2
unnamed: D6.1 (DOUT), TP1.1
unnamed: J1.A5 (CC1), R11.1
unnamed: J1.B5 (CC2), R10.2
unnamed: JP1.1 (A), R9.1
unnamed: JP2.1 (A), R17.1
unnamed: JP3.1 (A), R14.2
unnamed: R16.1, U5.5 (PROG)
VBATT: C2.1, C12.1, D3.A, J3.2 (+), U4.2 (CELL), U4.3 (VDD), U5.3 (V_{BAT}), U10.12 (V_BATT)
VIN: C10.1, C14.1, D2.C, D3.C, R13.1, U1.1 (VIN), U6.1 (VIN)
VUSB: C9.1, D2.A, J1.VBUS, JP3.2 (B), U2.5 (VCC), U5.4 (VIN), U10.10 (V_USB)
